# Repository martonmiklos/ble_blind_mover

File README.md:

## BLE blind mover

Control circuit designed to drive a Rollomatic Rollotube Tubular motor.

Design goals:
 - RTC feature for timed blind moving
 - BLE connectivity for programming and RTC sync
 - Integrated isolated 230V power supply for the low voltage parts

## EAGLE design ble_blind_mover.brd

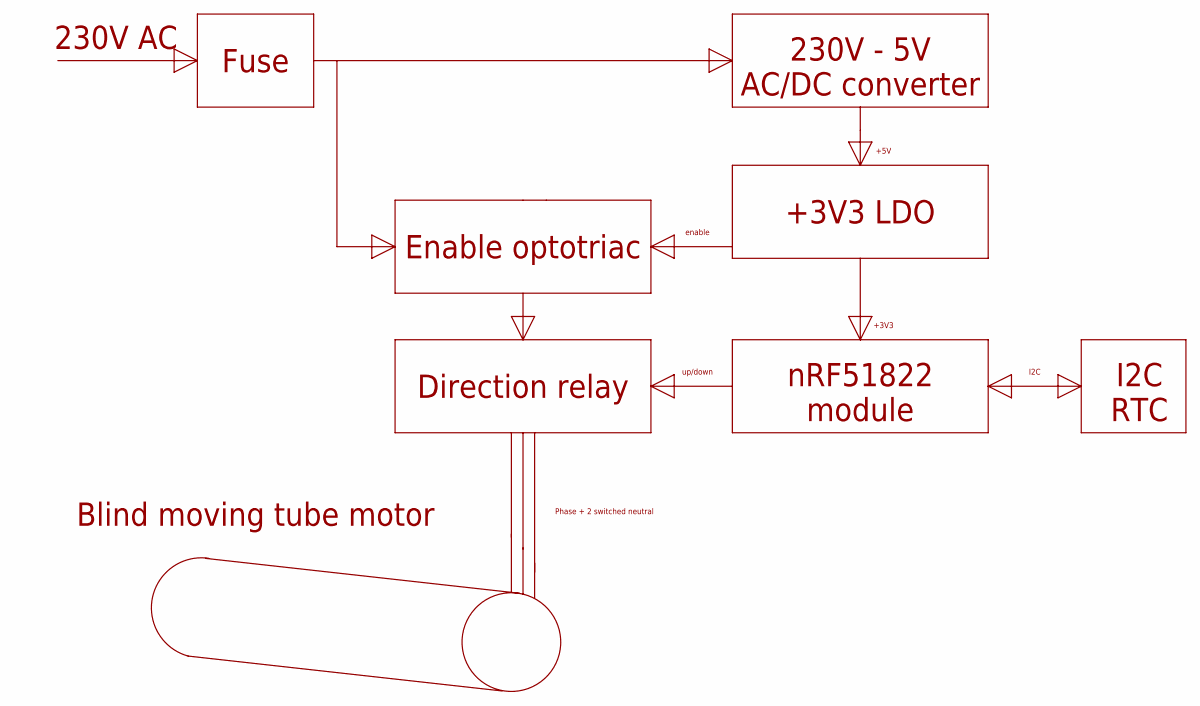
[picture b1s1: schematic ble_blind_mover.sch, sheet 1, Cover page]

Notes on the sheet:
Fuse
230V AC
230V - 5V AC/DC converter
Direction relay
nRF51822 module
Blind moving tube motor
up/down
+5V
Phase + 2 switched neutral
I2C RTC
I2C
+3V3 LDO
+3V3
Enable optotriac
enable

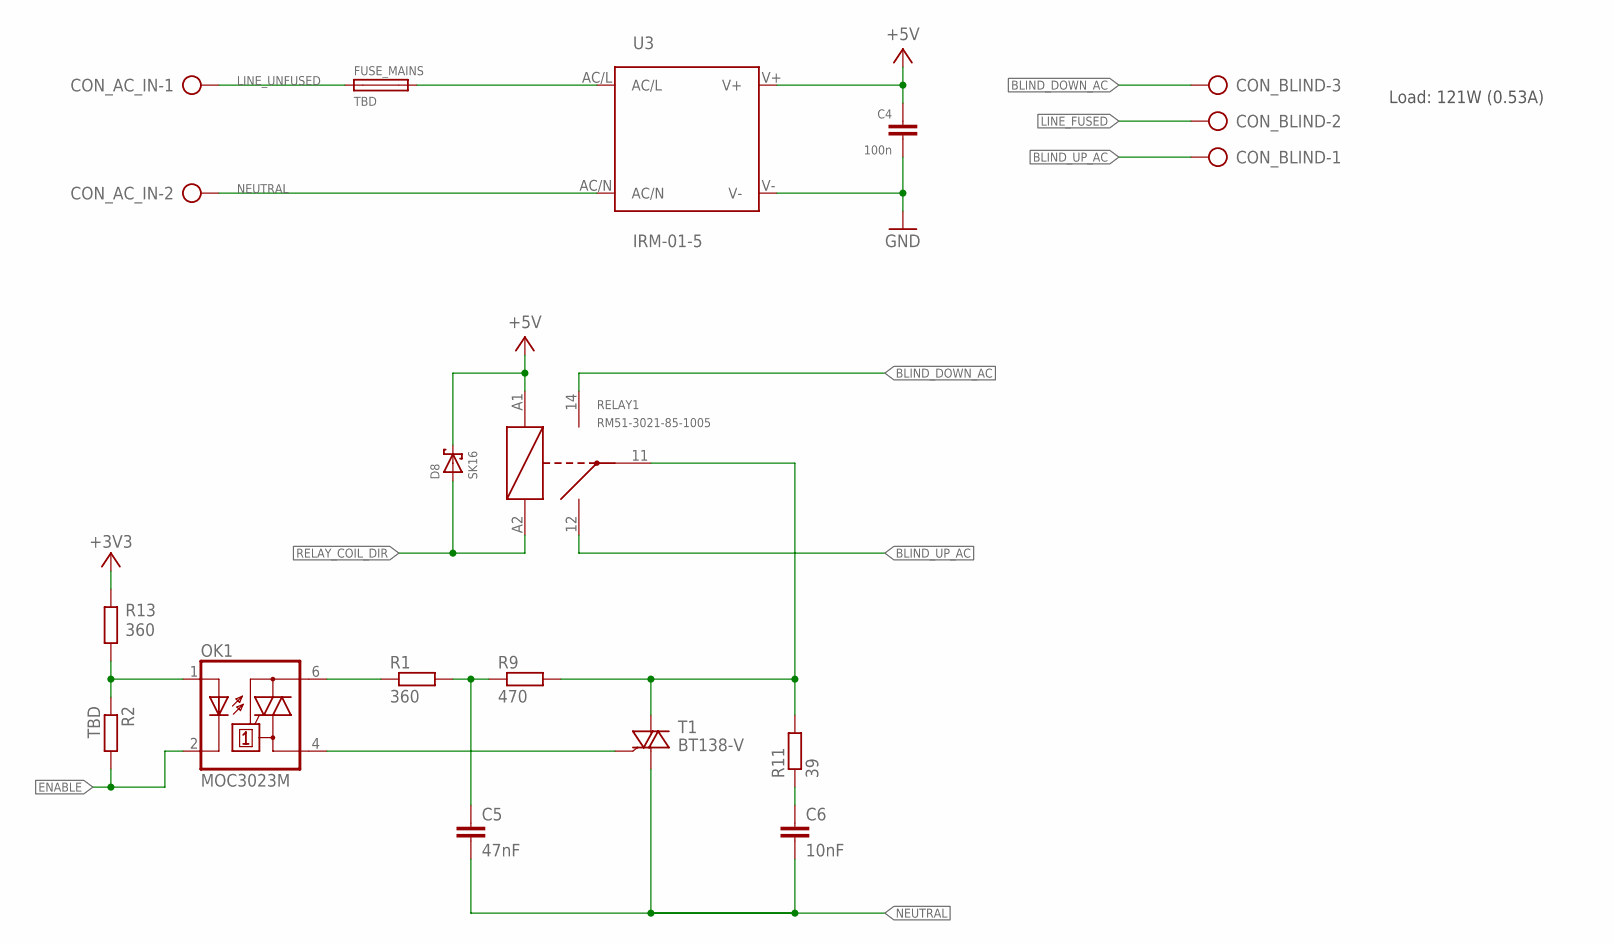
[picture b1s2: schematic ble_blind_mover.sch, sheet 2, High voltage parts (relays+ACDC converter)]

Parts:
C4: 100n; C0603
C5: 47nF; C025-030X050
C6: 10nF; C025-030X050
CON_AC_IN: AK500/2
CON_BLIND: AK500/3
D8: SK16; DO-214AC
FUSE_MAINS: TBD; SH22,5
OK1: MOC3023M; DIL06
R1: 360; R0805
R2: TBD; R0603
R9: 470; R0805
R11: 39; 0204V
R13: 360; R0603
RELAY1: RM51-3021-85-1005; RM50-3011-XX-XXXX
T1: BT138-V; TO220BV
U3: IRM-01-5; IRM_01/02

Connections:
+3V3: R13.1; also elsewhere on the board
+5V: C4.1, D8.C, RELAY1.A1, U3.V+; also elsewhere on the board
BLIND_DOWN_AC: CON_BLIND.3, RELAY1.14
BLIND_UP_AC: CON_BLIND.1, RELAY1.12
ENABLE: OK1.2 (C), R2.2; also elsewhere on the board
GND: C4.2, U3.V-; also elsewhere on the board
LINE_FUSED: CON_BLIND.2, FUSE_MAINS.2, U3.AC/L
LINE_UNFUSED: CON_AC_IN.1, FUSE_MAINS.1
LOAD_B: R9.2, R11.2, RELAY1.11, T1.T2 (A2)
MOC_AN: OK1.1 (A), R2.1, R13.2
MOC_OUT: OK1.6 (A2), R1.1
unnamed: C5.1, R1.2, R9.1
NEUTRAL: C5.2, C6.2, CON_AC_IN.2, T1.T1 (A1), U3.AC/N
RELAY_COIL_DIR: D8.A, RELAY1.A2; also elsewhere on the board
SNUB_MID: C6.1, R11.1
TRIAC_GET: OK1.4 (A1), T1.G

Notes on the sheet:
Load: 121W (0.53A)

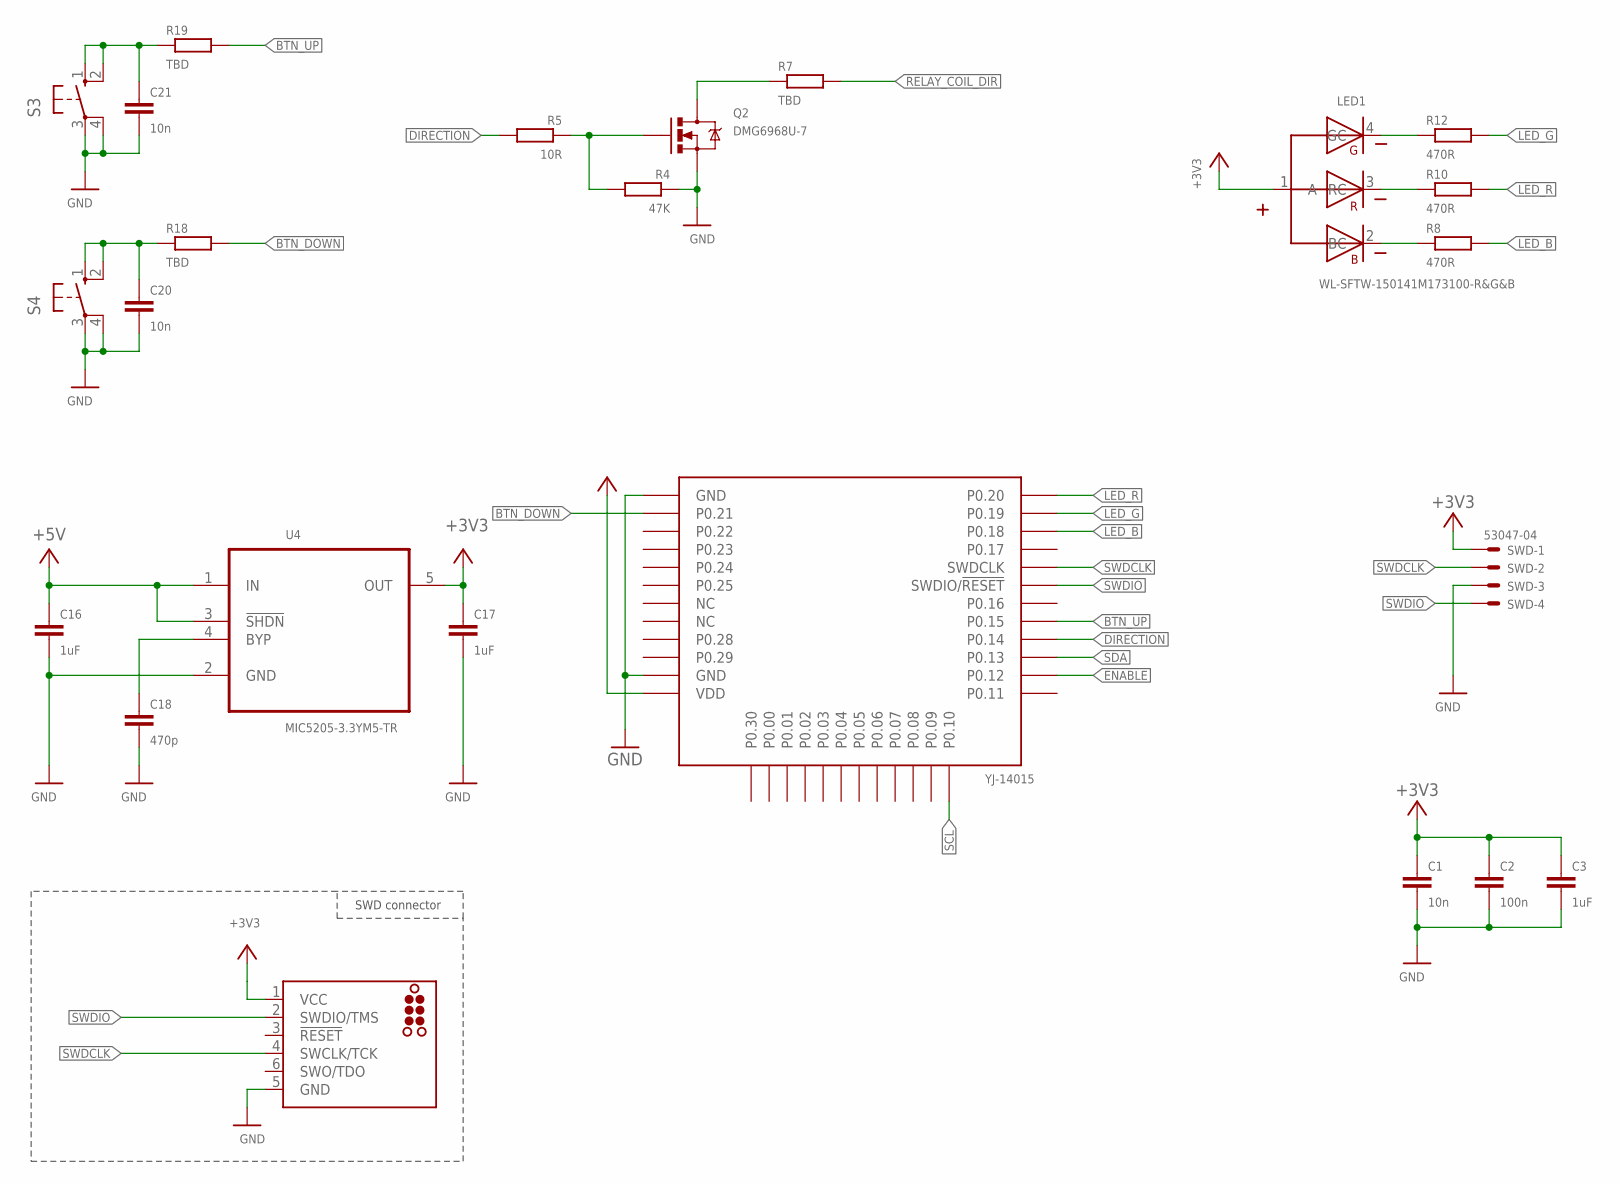
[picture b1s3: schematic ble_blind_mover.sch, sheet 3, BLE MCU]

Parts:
C1, C20, C21: 10n; C0603
C2: 100n; C0603
C3, C16, C17: 1uF; C0603
C18: 470p; C0603
J2: TC2030_SWD-MCP-NL; TC2030-MCP-NL
LED1: WL-SFTW-150141M173100-R&G&B; 3528-COMMON-ANODE
Q2: DMG6968U-7; SOT23-3
R4: 47K; R0603
R5: 10R; R0603
R7, R18, R19: TBD; R0603
R8, R10, R12: 470R; R0603
S3, S4: 10-XX; B3F-10XX
SWD: 53047-04
U2: YJ-14015
U4: MIC5205-3.3YM5-TR; SOT95P280X145-5N

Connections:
+3V3: C1.1, C2.1, C3.1, C17.1, J2.1 (VCC), LED1.1 (A), SWD.1, U2.VDD, U4.5 (OUT); also elsewhere on the board
+5V: C16.1, U4.1 (IN), U4.3 (!SHDN); also elsewhere on the board
BTN_DOWN: R18.2, U2.P.21 (P0.21)
BTN_DOWN_R: C20.1, R18.1, S4.1 (S), S4.2 (S1)
BTN_UP: R19.2, U2.P.15 (P0.15)
BTN_UP_R: C21.1, R19.1, S3.1 (S), S3.2 (S1)
DIRECTION: R5.2, U2.P.14 (P0.14)
ENABLE: U2.P.12 (P0.12); also elsewhere on the board
GND: C1.2, C2.2, C3.2, C16.2, C17.2, C18.2, C20.2, C21.2, J2.5 (GND), Q2.2 (S), R4.1, S3.3, S3.4 (P1), S4.3, S4.4 (P1), SWD.3, U2.GND, U2.GND@2 (GND), U4.2 (GND); also elsewhere on the board
LED2_B_R: LED1.2 (BC), R8.1
LED2_G_R: LED1.4 (GC), R12.1
LED2_R_R: LED1.3 (RC), R10.1
LED_B: R8.2, U2.P.18 (P0.18)
LED_G: R12.2, U2.P.19 (P0.19)
LED_R: R10.2, U2.P.20 (P0.20)
MOTOR_B_GATE_R: Q2.1 (G), R4.2, R5.1
RELAY_COIL_DIR: R7.2; also elsewhere on the board
RELAY_COIL_DIR_R: Q2.3 (D), R7.1
SCL: U2.P.10 (P0.10); also elsewhere on the board
SDA: U2.P.13 (P0.13); also elsewhere on the board
SWDCLK: J2.4 (SWCLK/TCK), SWD.2, U2.SWDCLK
SWDIO: J2.2 (SWDIO/TMS), SWD.4, U2.SWDIO (SWDIO/!RESET)
U4_BYPASS: C18.1, U4.4 (BYP)

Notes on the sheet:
SWD connector

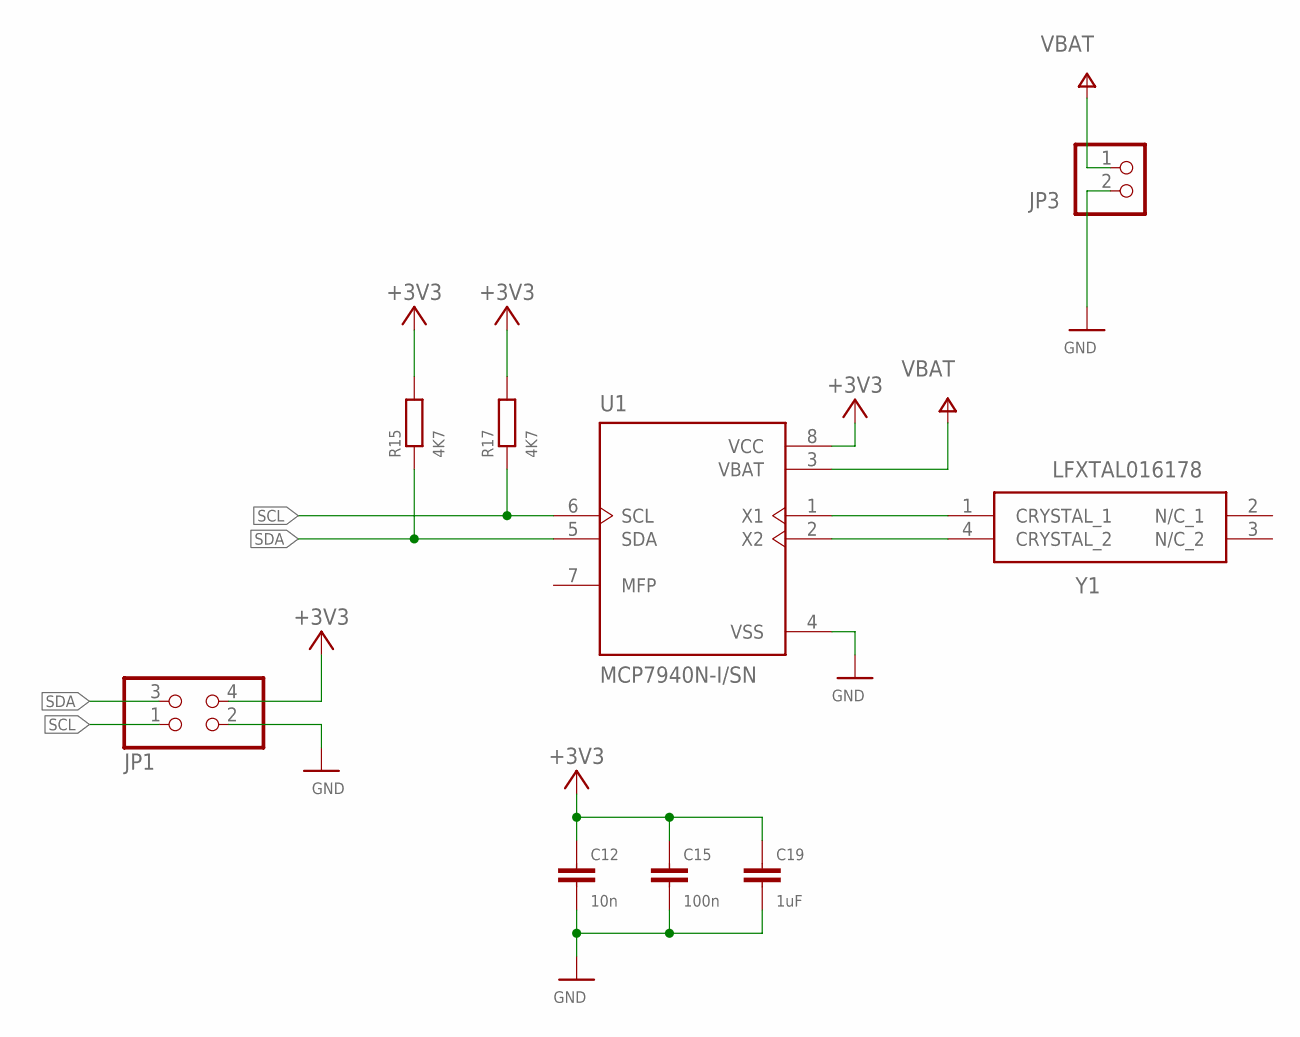
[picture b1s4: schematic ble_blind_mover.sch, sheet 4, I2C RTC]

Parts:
C12: 10n; C0603
C15: 100n; C0603
C19: 1uF; C0603
JP1: PINHD-2X2; 2X02
JP3: PINHD-1X2; 1X02
R15, R17: 4K7; R0603
U1: MCP7940N-I/SN; SOIC127P600X175-8N
Y1: LFXTAL016178; LFXTAL016178_1

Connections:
+3V3: C12.1, C15.1, C19.1, JP1.4, R15.2, R17.2, U1.8 (VCC); also elsewhere on the board
GND: C12.2, C15.2, C19.2, JP1.2, JP3.2, U1.4 (VSS); also elsewhere on the board
RTC_XTAL1: U1.1 (X1), Y1.1 (CRYSTAL_1)
RTC_XTAL2: U1.2 (X2), Y1.4 (CRYSTAL_2)
SCL: JP1.1, R17.1, U1.6 (SCL); also elsewhere on the board
SDA: JP1.3, R15.1, U1.5 (SDA); also elsewhere on the board
VBAT: JP3.1, U1.3 (VBAT)

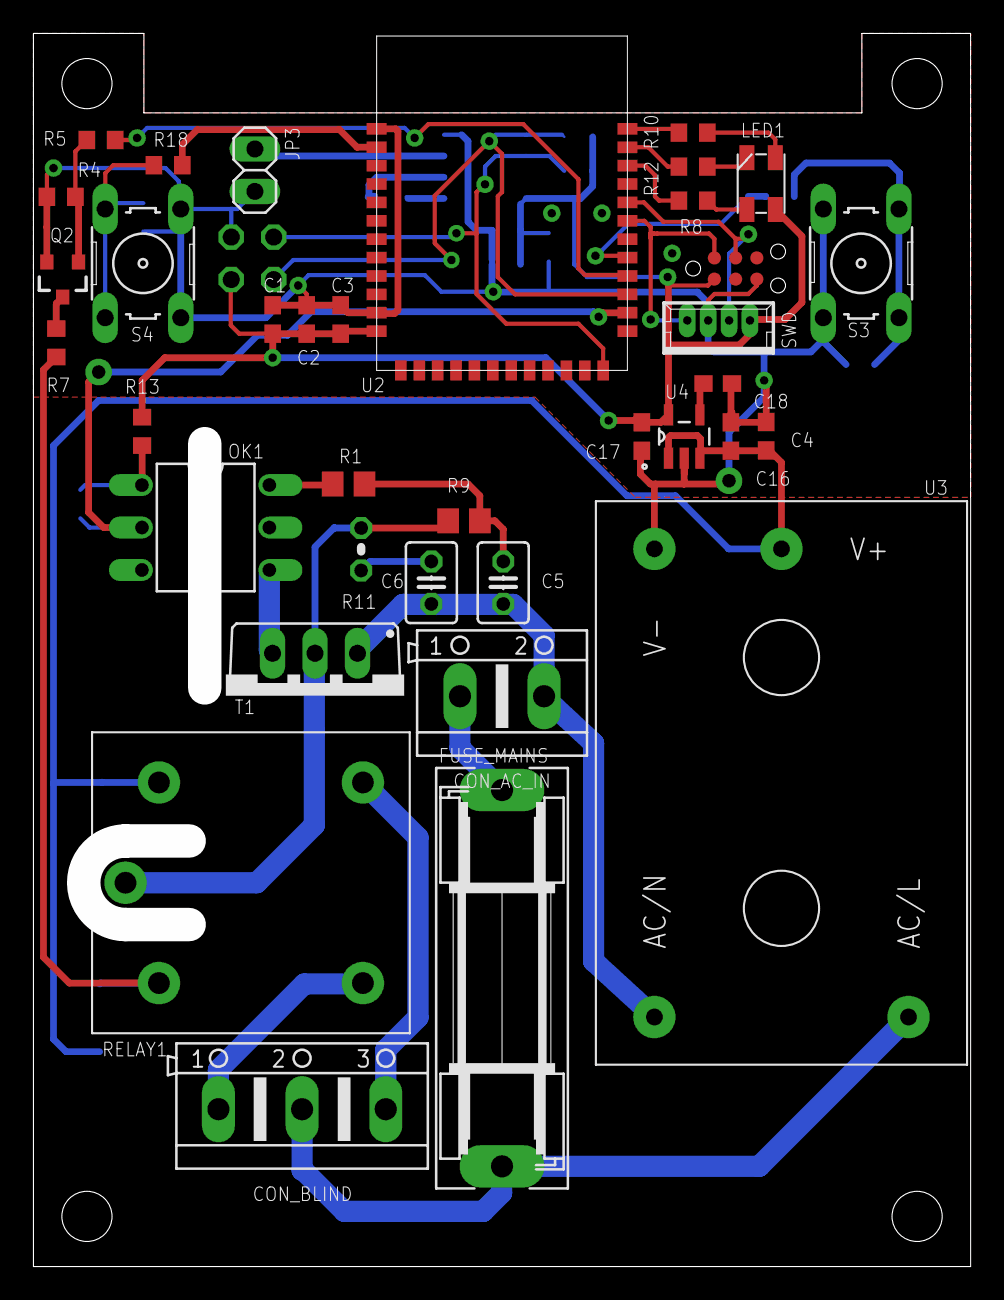
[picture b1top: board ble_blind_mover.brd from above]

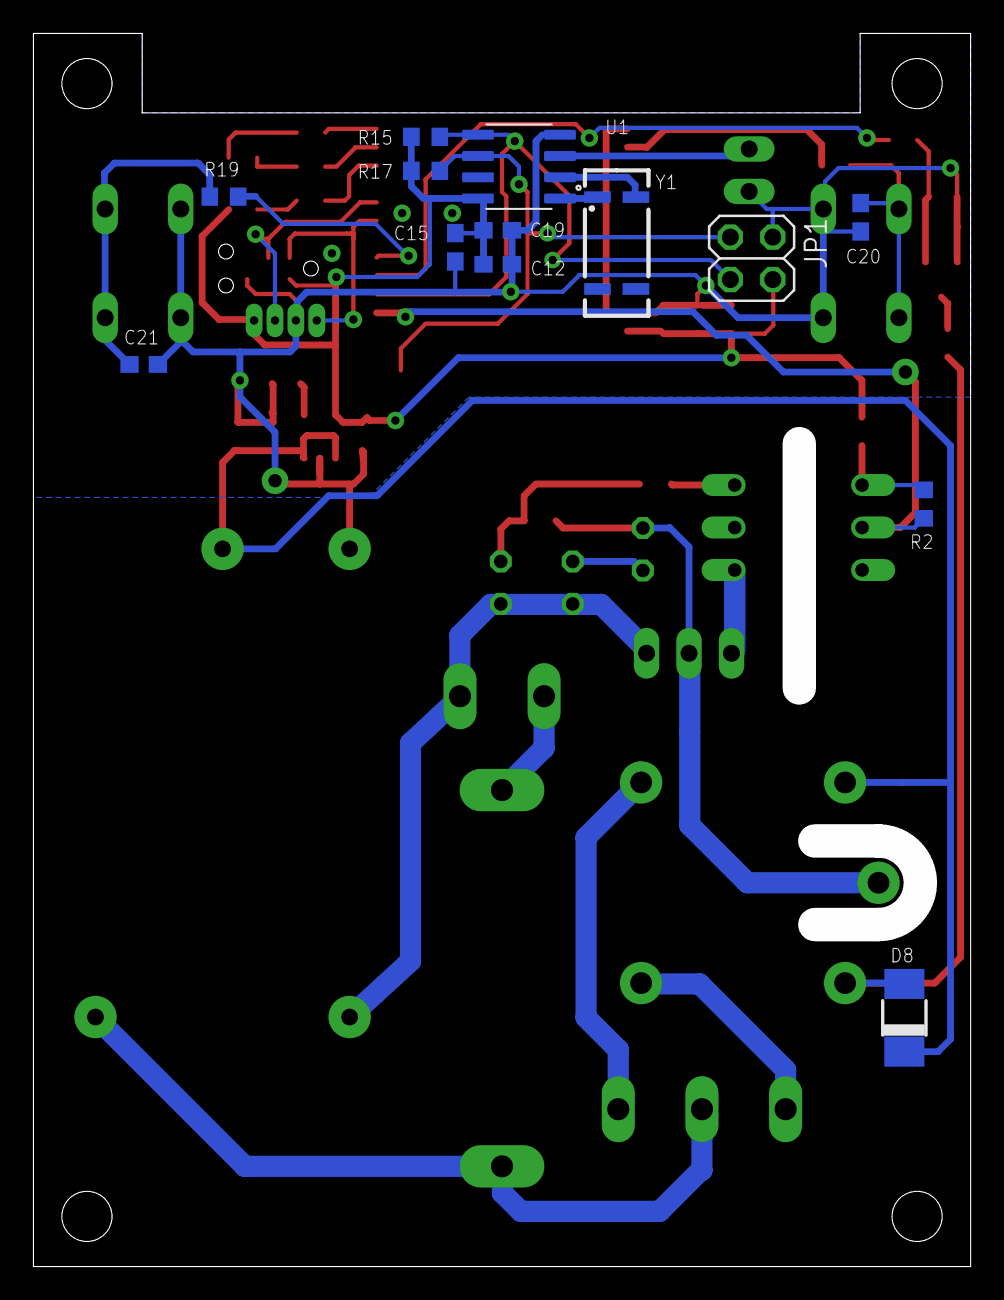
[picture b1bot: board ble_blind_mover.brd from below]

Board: 2 copper layers, 54.0 x 71.8 mm, 49 parts (13 on the bottom side), 37 nets.

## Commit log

2019-10-31 Working on SCH
2019-11-02 Naming all nets
2019-11-28 Daily save
2019-12-03 Brd routed, clearance adjustment still WIP
2019-12-04 Fixed board eouting for increased low/high voltage clearance
2019-12-05 Added power connecting pinheads
2020-02-29 Aligned silkscreen labels
2020-02-29 Added RTC
2020-02-29 - Add RTC to cover page - Add schematic PDF to the repo
2020-02-29 - Get rid from Viper PSU in favour of a Meanwell module - Make the contours to fit in a Kradex Z21 box
2020-04-23 MOved to a triac based design
2021-05-05 Added B2B connector for I2C

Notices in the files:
parts and their libraries:
Wurth_Elektronik_Optoelectronics_rev15b: Copyright: Würth Elektronik
SparkFun: Licensing: CC v3.0 Share-Alike You are welcome to use this library for commercial purposes.
relay-relpol: (C) 2014 Tomasz Boleslaw CEDRO, cederom@tlen.pl, http://www.tomek.cedro.info.
